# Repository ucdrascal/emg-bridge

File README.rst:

==========
emg-bridge
==========

.. image:: rev1/board.png
   :alt: Board screenshot

Description
===========

This board is for provding an interface between multiple Motion Labs Y03
amplifiers and a DAQ. The board provides RJ25 (6p6c modular jack) connectors
for plugging in up to 8 amplifiers. 5V power from either a barrel plug ("wall
wart") or USB-B is converted to +/-5V (isolated from power source, which
powers the amplifiers. The signal output from each amplifier is output through
a flat ribbon cable to the DAQ. A single ground electrode can be plugged in to 
a header pin.

License
=======

The contents of this repository are licensed under the `CC-BY 4.0 license`_.

.. REFERENCES
.. _`CC-BY 4.0 license`: https://creativecommons.org/licenses/by/4.0/

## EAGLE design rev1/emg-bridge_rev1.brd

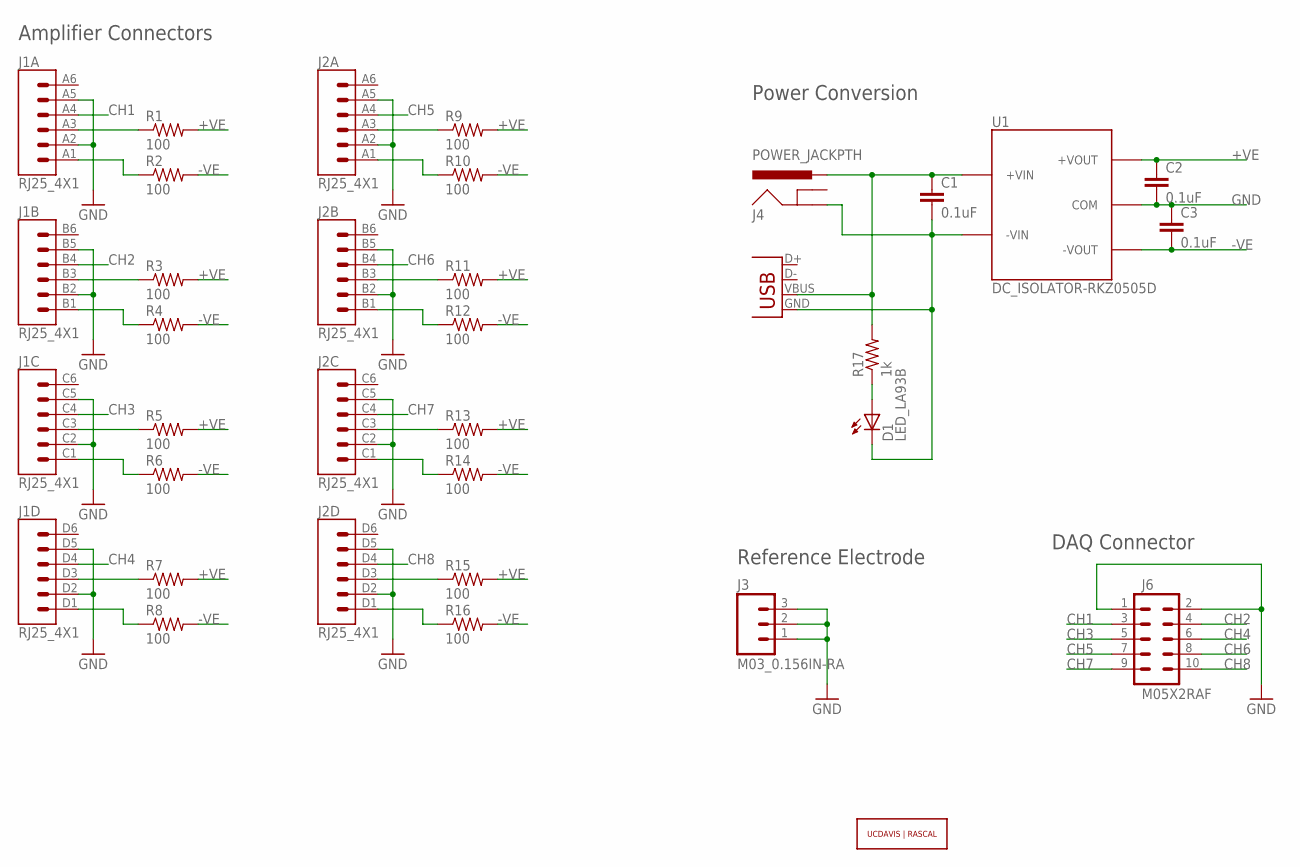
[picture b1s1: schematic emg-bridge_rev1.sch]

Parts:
C1, C2, C3: 0.1uF; 0805
D1: LED_LA93B; LED_RA
J1, J2: RJ25_4X1
J3: M03_0.156IN-RA; TE_640389-3
J4: POWER_JACKPTH; POWER_JACK_PTH
J5: USB-B; USB-B-PTH
J6: M05X2RAF; 2X5-RAF
R1, R2, R3, R4, R5, R6, R7, R8, R9, R10, R11, R12, R13, R14, R15, R16: 100; 0805
R17: 1k; 0805
U1: DC_ISOLATOR-RKZ0505D; SIP7
U$1: UCDAVIS-RASCAL_LOGO-2LINE; UCDAVIS-RASCAL_LOGO

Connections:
+VE: C2.1, R1.2, R3.2, R5.2, R7.2, R9.2, R11.2, R13.2, R15.2, U1.7 (+VOUT)
-VE: C3.2, R2.2, R4.2, R6.2, R8.2, R10.2, R12.2, R14.2, R16.2, U1.5 (-VOUT)
CH1: J1.A4, J6.3
CH2: J1.B4, J6.4
CH3: J1.C4, J6.5
CH4: J1.D4, J6.6
CH5: J2.A4, J6.7
CH6: J2.B4, J6.8
CH7: J2.C4, J6.9
CH8: J2.D4, J6.10
DGND: C1.2, D1.K (C), J4.GND, J5.GND, U1.2 (-VIN)
GND: C2.2, C3.1, J1.A2, J1.A5, J1.B2, J1.B5, J1.C2, J1.C5, J1.D2, J1.D5, J2.A2, J2.A5, J2.B2, J2.B5, J2.C2, J2.C5, J2.D2, J2.D5, J3.1, J3.2, J3.3, J6.1, J6.2, U1.6 (COM)
unnamed: J1.A1, R2.1
unnamed: C1.1, J4.PWR, J5.VBUS, R17.2, U1.1 (+VIN)
unnamed: J1.A3, R1.1
unnamed: D1.A, R17.1
unnamed: J1.B1, R4.1
unnamed: J1.B3, R3.1
unnamed: J1.C1, R6.1
unnamed: J1.C3, R5.1
unnamed: J1.D1, R8.1
unnamed: J1.D3, R7.1
unnamed: J2.A1, R10.1
unnamed: J2.A3, R9.1
unnamed: J2.B1, R12.1
unnamed: J2.B3, R11.1
unnamed: J2.C1, R14.1
unnamed: J2.C3, R13.1
unnamed: J2.D1, R16.1
unnamed: J2.D3, R15.1

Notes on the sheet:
Amplifier Connectors
Power Conversion
DAQ Connector
Reference Electrode

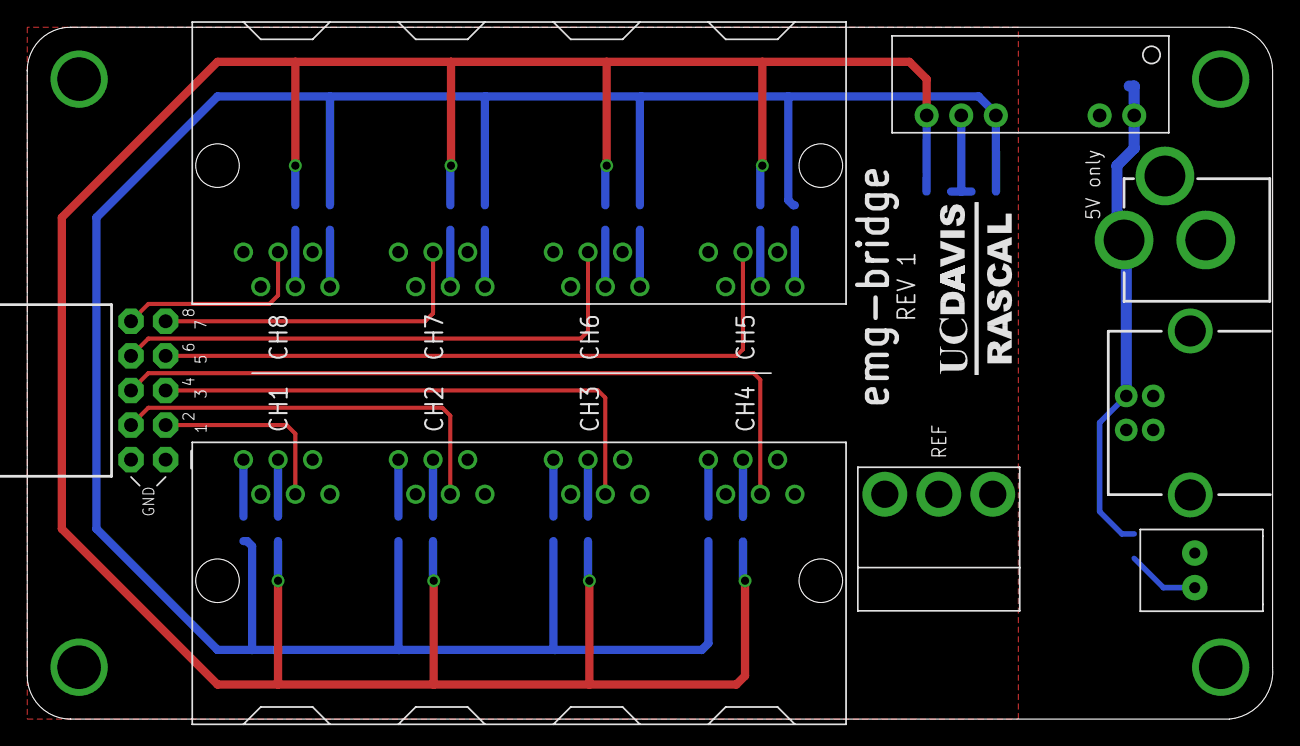
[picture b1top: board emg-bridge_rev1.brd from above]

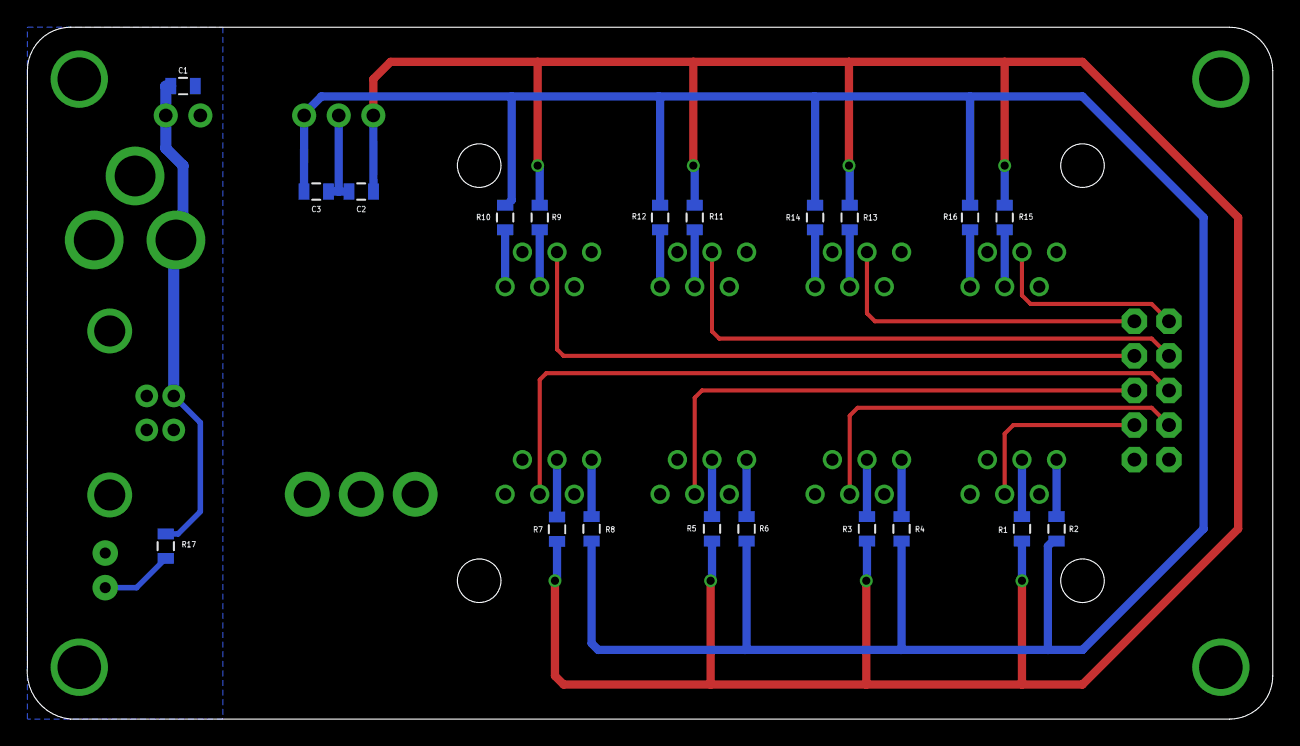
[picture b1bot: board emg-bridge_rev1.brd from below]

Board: 2 copper layers, 91.5 x 50.8 mm, 29 parts (20 on the bottom side), 30 nets.

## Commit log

2014-01-24 Initial commit.
2014-01-24 Added small note on the 2x5 header/connector to identify the red wire in the cable.
2014-01-25 Updated parts from eagle-lib. Worked out pinouts for all connectors.
2014-01-27 Schematic cleaned up and board layout/routing rough draft completed.
2014-01-27 Updated for eagle-lib changes. Finished up schematic.
2014-01-28 Finished up layout and routing. Revision 1 complete.
2014-01-28 Updated BOM.
2014-01-28 Added channel numbers on silkscreen.
2014-01-29 Realization: the MC USB-1608G DAQ can only output 10mA for power, so the power circuitry has been completely reworked. Now with 3kV isolation!
2014-01-29 Added power jack.
2014-01-29 Added power jack to BOM.
2014-01-29 Added LED.
2014-01-29 Changed a cap label to vector font.
2014-01-30 Minor changes. Revision 1 should really be ready this time.
2014-01-30 Revision 1 ordered and archived.
2018-02-12 Updated README
    - added screenshot of board layout
    - added LICENSE

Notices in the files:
parts and their libraries:
SparkFun-Passives: Licensing: CC v3.0 Share-Alike You are welcome to use this library for commercial purposes.
